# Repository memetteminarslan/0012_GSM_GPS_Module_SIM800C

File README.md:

# 0012_GSM_GPS_Module_SIM800C
You are seeing a large number of widely used GSM and GPRS modules in electronic development kits. More information coming sooon...

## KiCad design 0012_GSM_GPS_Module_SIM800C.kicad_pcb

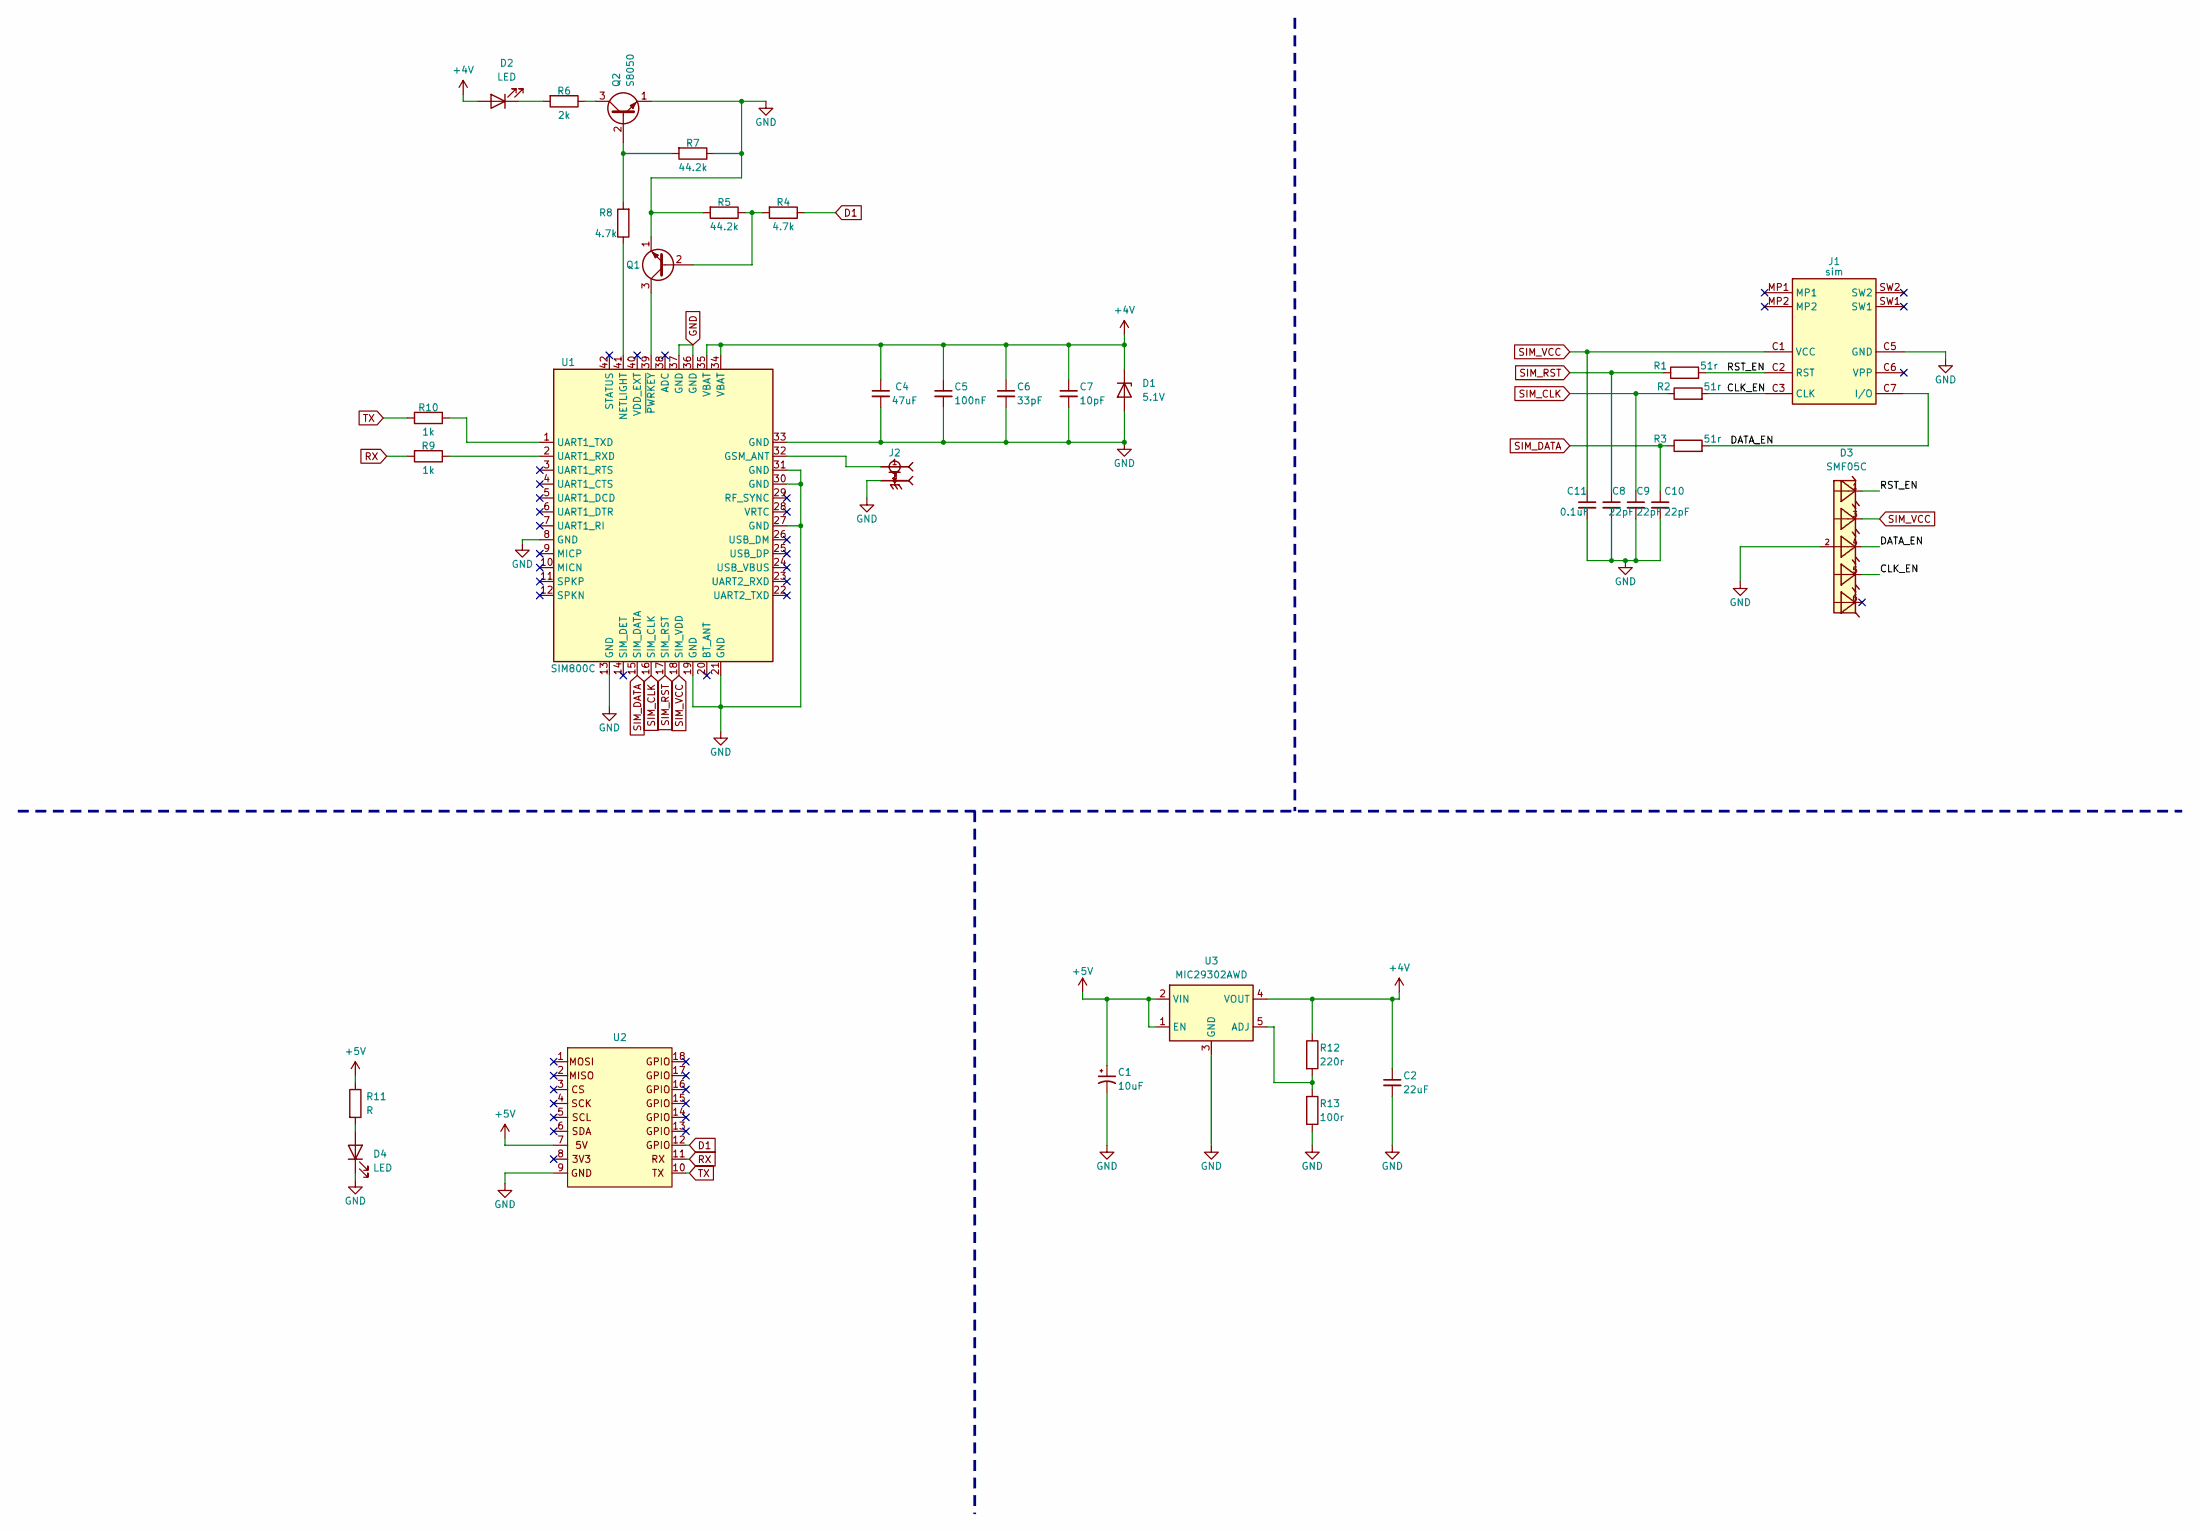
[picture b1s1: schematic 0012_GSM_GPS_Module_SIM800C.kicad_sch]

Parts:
C1: 10uF; CP_EIA-2012-12_Kemet-R
C2: 22uF; C_0603_1608Metric
C4: 47uF; C_0603_1608Metric
C5: 100nF; C_0603_1608Metric
C6: 33pF; C_0603_1608Metric
C7: 10pF; C_0603_1608Metric
C8, C9, C10: 22pF; C_0603_1608Metric
C11: 0.1uF; C_0603_1608Metric
D1: 5.1V; D_0603_1608Metric
D2, D4: LED; LED_0603_1608Metric
D3: SMF05C; SC70-6
J1: sim; LKLS1SIM06462PH185R; Manufacturer_Part_Number L-KLS1-SIM-064-(6+2)P-H1.85-R
J2: 20279-001E-01; L-KLS1-IPEX-20279-001E-0; PARTREV 21
Q1, Q2: S8050; SOT-23
R1, R2, R3: 51r; R_0603_1608Metric
R4, R8: 4.7k; R_0603_1608Metric
R5, R7: 44.2k; R_0603_1608Metric
R6: 2k; R_0603_1608Metric
R9, R10: 1k; R_0603_1608Metric
R11: R; R_0603_1608Metric
R12: 220r; R_0603_1608Metric
R13: 100r; R_0603_1608Metric
U1: SIM800C; SIMCom_SIM800C
U2: pin_header_5-3
U3: MIC29302AWD; TO-252-5_TabPin3

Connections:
+4V: C2.1, C4.1, C5.1, C6.1, C7.1, D1.1 (K), D2.2 (A), R12.1, U1.34 (VBAT), U1.35 (VBAT), U3.4 (VOUT)
+5V: C1.1, R11.1, U2.7, U3.1 (EN), U3.2 (VIN)
/CLK_EN: D3.5, J1.C3 (CLK), R2.2
/DATA_EN: D3.4, J1.C7 (I/O), R3.2
/RST_EN: D3.1, J1.C2 (RST), R1.2
D1: R4.1, U2.12
GND: C1.2, C2.2, C4.2, C5.2, C6.2, C7.2, C8.2, C9.2, C10.2, C11.2, D1.2 (A), D3.2, D4.1 (K), J1.C5 (GND), J2.2, J2.3, Q1.1 (E), Q2.1 (E), R5.2, R7.1, R13.2, U1.8 (GND), U1.13 (GND), U1.19 (GND), U1.21 (GND), U1.27 (GND), U1.30 (GND), U1.31 (GND), U1.33 (GND), U1.36 (GND), U1.37 (GND), U2.9, U3.3 (GND)
unnamed: D2.1 (K), R6.2
unnamed: D4.2 (A), R11.2
unnamed: Q1.2 (B), R4.2, R5.1
unnamed: Q1.3 (C), U1.39 (~PWRKEY)
unnamed: Q2.2 (B), R7.2, R8.2
unnamed: Q2.3 (C), R6.1
unnamed: J2.1, U1.32 (GSM_ANT)
unnamed: R8.1, U1.41 (NETLIGHT)
unnamed: R9.1, U1.2 (UART1_RXD)
unnamed: R10.1, U1.1 (UART1_TXD)
unnamed: R12.2, R13.1, U3.5 (ADJ)
RX: R9.2, U2.11
SIM_CLK: C9.1, R2.1, U1.16 (SIM_CLK)
SIM_DATA: C10.1, R3.1, U1.15 (SIM_DATA)
SIM_RST: C8.1, R1.1, U1.17 (SIM_RST)
SIM_VCC: C11.1, D3.3, J1.C1 (VCC), U1.18 (SIM_VDD)
TX: R10.2, U2.10

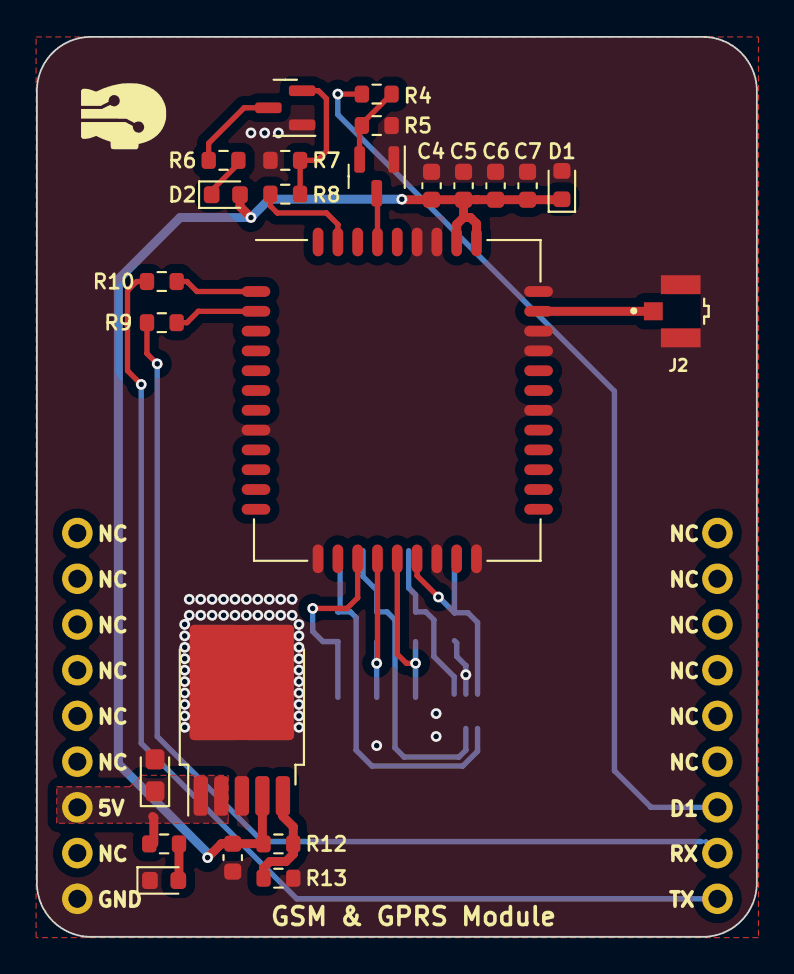
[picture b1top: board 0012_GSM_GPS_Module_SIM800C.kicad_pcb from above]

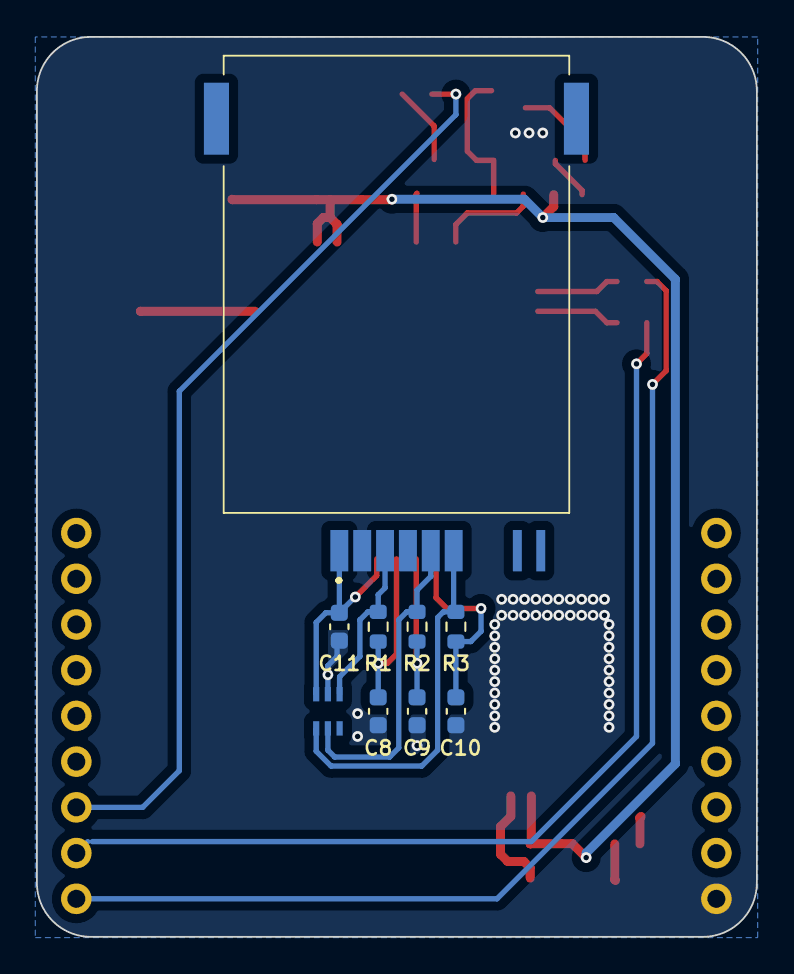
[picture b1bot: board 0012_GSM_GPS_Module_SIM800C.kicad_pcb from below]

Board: 2 copper layers, 40.0 x 50.0 mm, 34 parts (9 on the bottom side), 24 nets.
